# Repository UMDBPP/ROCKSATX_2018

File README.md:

# ROCKSATX_2018
BPP 2018 Rocksat - X

Payload: TERP (Tribocharging Experiment and Robotic Performance)

Contains two experiments: STAR and SCAMP

## STAR
Stratification and Tribocharging Analysis of Regolith (STAR)

## SCAMP
Space Characterization and Assessment of Manipulator Performance

# Organization
CAD/: All mechanical design files (CAD)

Payload_Integration/:  Files documenting external interfaces of TERP

SCAMP/: SCAMP-specific design files

STAR/: STAR-specific design files

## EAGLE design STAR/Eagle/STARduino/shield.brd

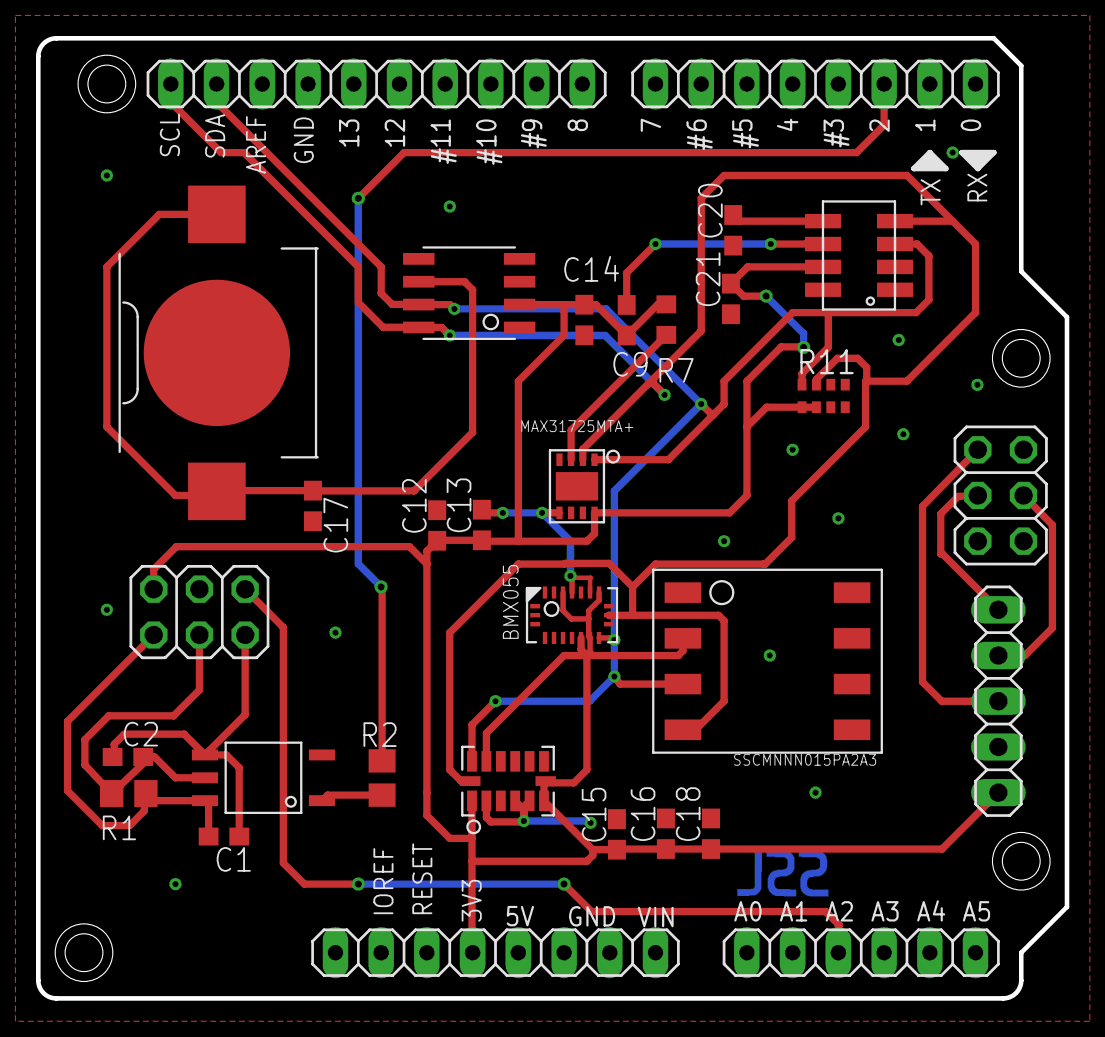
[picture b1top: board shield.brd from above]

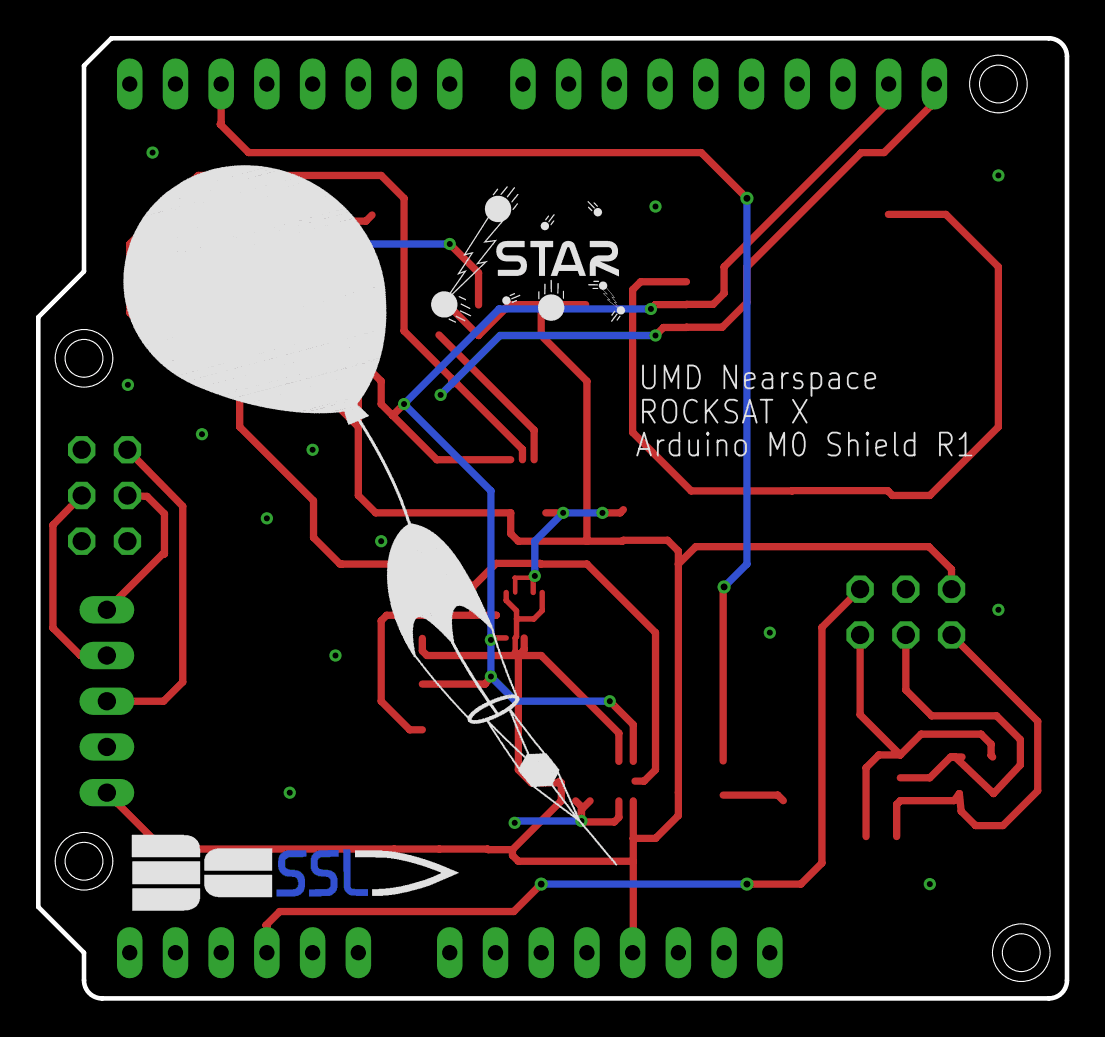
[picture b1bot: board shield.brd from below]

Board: 2 copper layers, 57.1 x 53.3 mm, 34 parts (3 on the bottom side), 16 nets.

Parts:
AD: 6x1F-H8.5; 1X06
ADXL375BCCZ: ADXL375BCCZ; LGA-14
B1: CR1025
BMX055: BMX055; LGA-20
C1, C9, C12, C13, C14, C16, C18, C20: 100nF; C0603
C2: 15pf; C0603
C15: 10uF; C0603
C17: 1nF; C0603
C21: 220nF; C0603
CC2: CC2
DS3231MZ+: DS3231MZ+; SOIC-8
IMAG2: STAR; STAR_.3IN
IOH: 10x1F-H8.5; 1X10
IOL: 8x1F-H8.5; 1X08
JP1: 1X05
JP2, JP3: 2X03
MAX31725MTA+: MAX31725MTA+; DFN-8
MOTORDRIVER: FODM8061-D; SO5
POWER: 8x1F-H8.5; 1X08
R1, R2: 442; R0805
R7: 4.7k; R0603
R11: 4.7k; 0603-ARV
U12: SSCMNNN015PA2A3; HSC-SMT-8
U$1: BALLOON
U$2: SSLORIG; SSL

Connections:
+3V3: ADXL375BCCZ.1, ADXL375BCCZ.6, ADXL375BCCZ.7, ADXL375BCCZ.12, BMX055.3, BMX055.7, BMX055.12, BMX055.13, C9.1, C12.1, C13.1, C14.1, C15.1, C16.1, C18.1, C21.2, CC2.P$7, DS3231MZ+.2, JP1.1, JP3.2, MAX31725MTA+.8, POWER.4, R7.2, R11.5, R11.6, U12.2
BIAS_REF: AD.3, JP3.6
GND: ADXL375BCCZ.2, ADXL375BCCZ.4, ADXL375BCCZ.5, B1.3, BMX055.4, BMX055.6, BMX055.17, BMX055.20, C9.2, C12.2, C13.2, C14.2, C15.2, C16.2, C17.2, C18.2, C20.1, C21.1, CC2.P$6, DS3231MZ+.5, IOH.7, JP1.2, JP2.6, JP3.4, MAX31725MTA+.4, MAX31725MTA+.5, MAX31725MTA+.6, MAX31725MTA+.7, MAX31725MTA+.9, MOTORDRIVER.P$3, POWER.6, POWER.7, U12.1
MISO: JP1.3, JP2.1
MOSI: JP1.4, JP2.4
MOTOR: IOL.3, R2.2
MOTOR_GND: C1.2, C2.2, JP3.5, MOTORDRIVER.P$4
MOTOR_SIGNAL: C2.1, JP3.3, MOTORDRIVER.P$5, R1.2
MOTOR_VCC: C1.1, JP3.1, MOTORDRIVER.P$6, R1.1
unnamed: C20.2, CC2.P$5
unnamed: MOTORDRIVER.P$1, R2.1
unnamed: MAX31725MTA+.3, R7.1
unnamed: B1.1, B1.2, C17.1, DS3231MZ+.6
SCK: JP1.5, JP2.3
SCL: ADXL375BCCZ.14, BMX055.9, CC2.P$4, DS3231MZ+.8, IOH.10, MAX31725MTA+.2, R11.3, U12.4
SDA: ADXL375BCCZ.13, BMX055.11, CC2.P$3, DS3231MZ+.7, IOH.9, MAX31725MTA+.1, R11.4, U12.3

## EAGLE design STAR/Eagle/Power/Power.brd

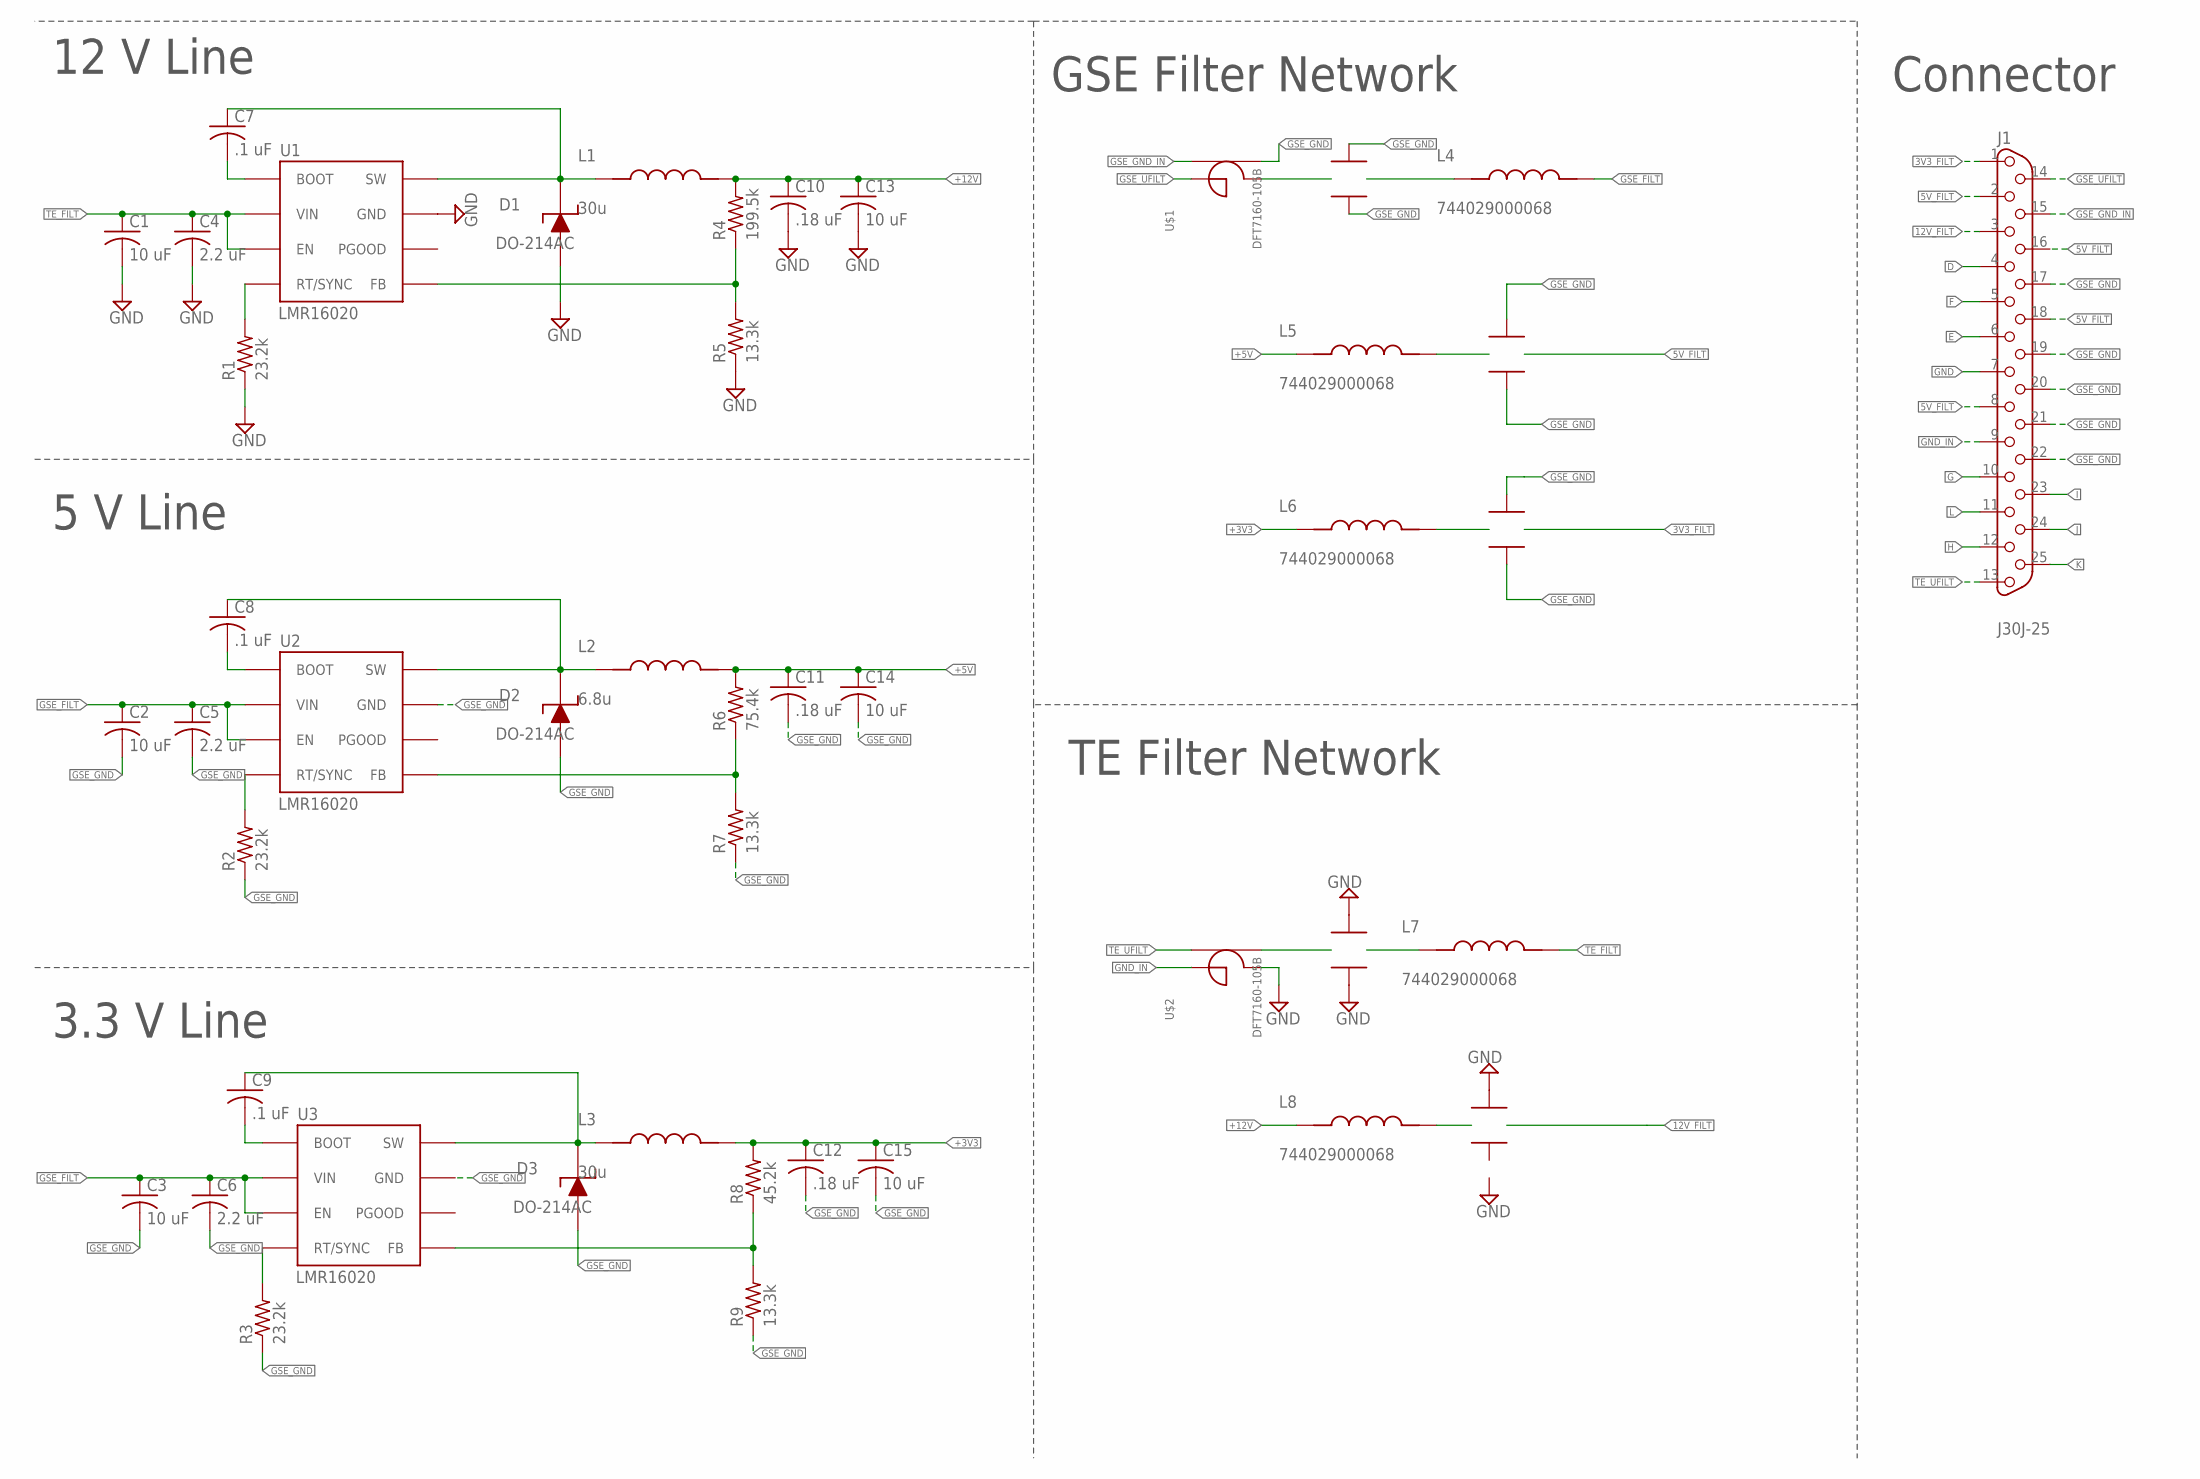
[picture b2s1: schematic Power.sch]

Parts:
C1, C2, C3: 10 uF; C1210
C4, C5, C6: 2.2 uF; C1210
C7, C8, C9: .1 uF; C0603
C10, C11, C12: .18 uF; C0603
C13, C14, C15: 10 uF; C0603
D1, D2, D3: DO-214AC
J1: J30J-25; ZKN-25
L1: 30u; 7050
L2: 6.8u; 7050
L3: 30u; 1365
L4, L5, L6, L7, L8: 744029000068; 2813
R1, R2, R3: 23.2k; R0603
R4: 199.5k; R0603
R5, R7, R9: 13.3k; R0603
R6: 75.4k; R0603
R8: 45.2k; R0603
U1, U2, U3: LMR16020; SO8
U$1, U$2: DFT7160-105B; DFT7160
U$3, U$4, U$5, U$6, U$7: 1410J0500404MXTE03; 1410

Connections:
3V3_FILT: J1.1, U$5.P$4
5V_FILT: J1.2, J1.8, J1.16, J1.18, U$4.P$4
12V_FILT: J1.3, U$7.P$4
+3V3: C12.1, C15.1, L3.P$2, L6.P$1, R8.2
+5V: C11.1, C14.1, L2.P$2, L5.P$1, R6.2
+12V: C10.1, C13.1, L1.P$2, L8.P$1, R4.2
D: J1.4
E: J1.6
F: J1.5
G: J1.10
GND: C1.2, C4.2, C10.2, C13.2, D1.P$1, J1.7, R1.1, R5.1, U1.P$7 (GND), U1.PAD (GND), U$2.P$4, U$6.P$2, U$6.P$3, U$7.P$3
GND_IN: J1.9, U$2.P$1
GSE_FILT: C2.1, C3.1, C5.1, C6.1, L4.P$2, U2.P$2 (VIN), U2.P$3 (EN), U3.P$2 (VIN), U3.P$3 (EN)
GSE_GND: C2.2, C3.2, C5.2, C6.2, C11.2, C12.2, C14.2, C15.2, D2.P$1, D3.P$1, J1.17, J1.19, J1.20, J1.21, J1.22, R2.1, R3.1, R7.1, R9.1, U2.P$7 (GND), U2.PAD (GND), U3.P$7 (GND), U3.PAD (GND), U$1.P$3, U$3.P$2, U$3.P$3, U$4.P$2, U$4.P$3, U$5.P$2, U$5.P$3
GSE_GND_IN: J1.15, U$1.P$2
GSE_UFILT: J1.14, U$1.P$1
H: J1.12
I: J1.23
J: J1.24
K: J1.25
L: J1.11
unnamed: R3.2, U3.P$4 (RT/SYNC)
unnamed: C9.1, D3.P$2, L3.P$1, U3.P$8 (SW)
unnamed: R2.2, U2.P$4 (RT/SYNC)
unnamed: C8.2, U2.P$1 (BOOT)
unnamed: C8.1, D2.P$2, L2.P$1, U2.P$8 (SW)
unnamed: C9.2, U3.P$1 (BOOT)
unnamed: R1.2, U1.P$4 (RT/SYNC)
unnamed: R8.1, R9.2, U3.P$5 (FB)
unnamed: R6.1, R7.2, U2.P$5 (FB)
unnamed: C7.2, U1.P$1 (BOOT)
unnamed: C7.1, D1.P$2, L1.P$1, U1.P$8 (SW)
unnamed: R4.1, R5.2, U1.P$5 (FB)
unnamed: U$1.P$4, U$3.P$4
unnamed: U$2.P$3, U$6.P$5
unnamed: L4.P$1, U$3.P$5
unnamed: L5.P$2, U$4.P$5
unnamed: L6.P$2, U$5.P$5
unnamed: L7.P$1, U$6.P$4
unnamed: L8.P$2, U$7.P$5
TE_FILT: C1.1, C4.1, L7.P$2, U1.P$2 (VIN), U1.P$3 (EN)
TE_UFILT: J1.13, U$2.P$2

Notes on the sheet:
12 V Line
5 V Line
3.3 V Line
GSE Filter Network
TE Filter Network
Connector

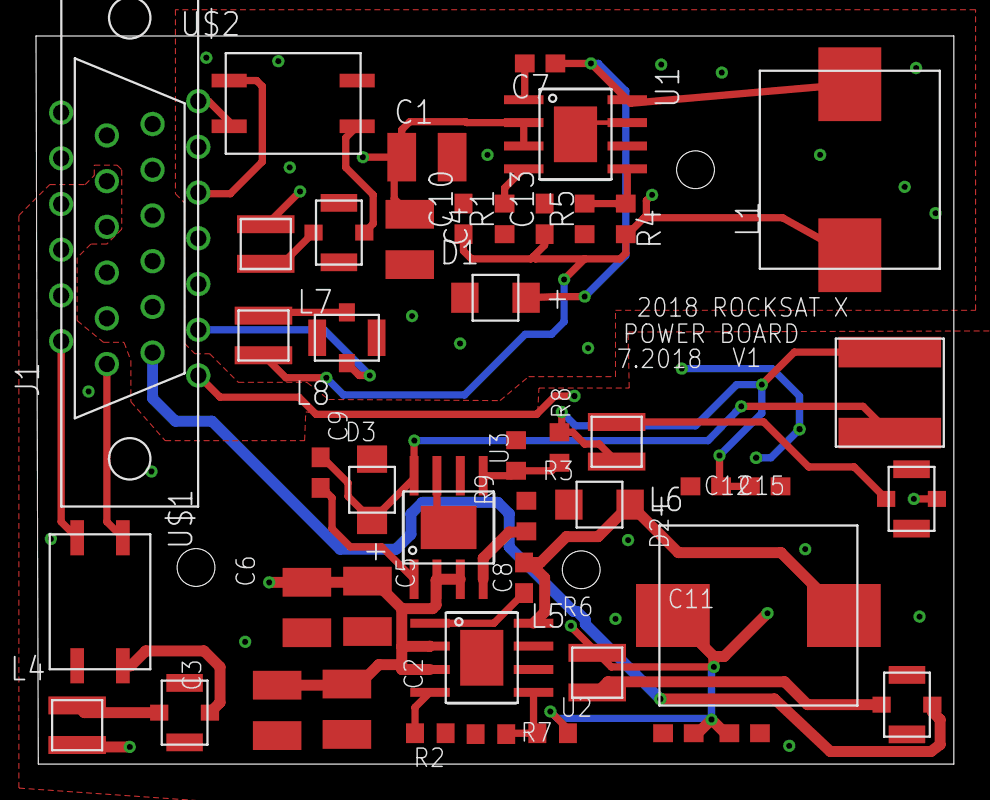
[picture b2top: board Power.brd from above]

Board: 2 copper layers, 51.0 x 40.4 mm, 46 parts (0 on the bottom side), 33 nets.

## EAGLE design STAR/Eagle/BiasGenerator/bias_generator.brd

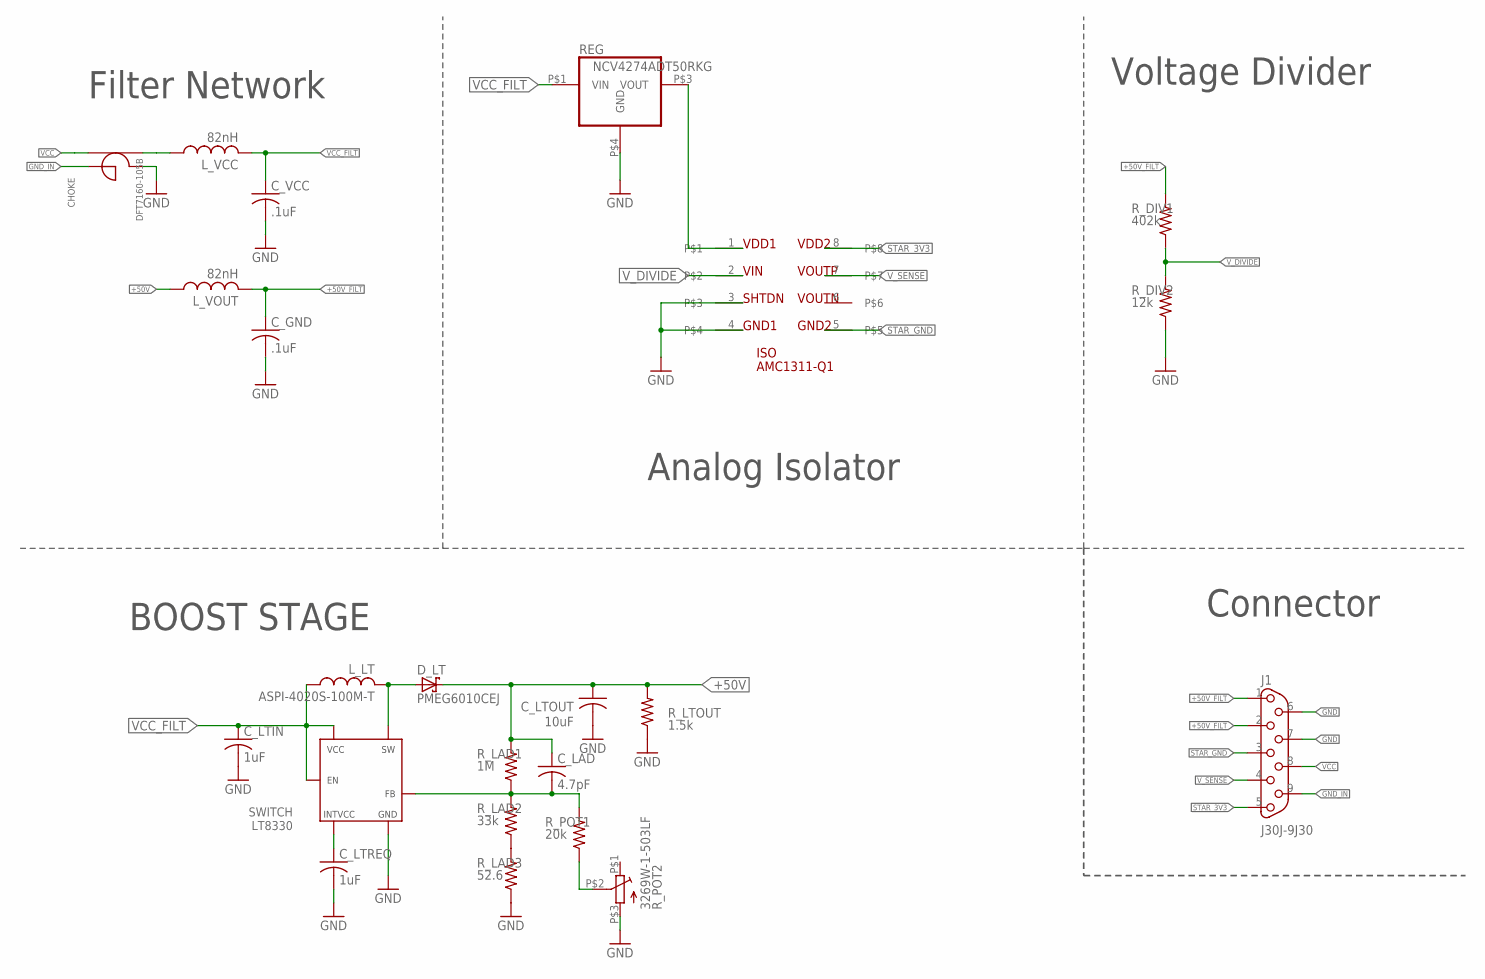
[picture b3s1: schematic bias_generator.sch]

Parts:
CHOKE: DFT7160-105B; DFT7160
C_GND: .1uF; C0603
C_LAD: 4.7pF; 0603
C_LTIN: 1uF; 0603
C_LTOUT: 10uF; 2J-LEAD
C_LTREQ: 1uF; 0603
C_VCC: .1uF; C0603
D_LT: PMEG6010CEJ; SOD323
ISO: AMC1311-Q1; SOIC8
J1: J30J-9J30; ZKN-9-J30
L_LT: ASPI-4020S-100M-T; 4MM
L_VCC: 82nH; C0603
L_VOUT: 82nH; C0603
REG: NCV4274ADT50RKG; DPAK
R_DIV1: 402k; R0603
R_DIV2: 12k; R0603
R_LAD1: 1M; R0603
R_LAD2: 33k; R0603
R_LAD3: 52.6; R0603
R_LTOUT: 1.5k; R2512
R_POT1: 20k; R0603
R_POT2: 3269W-1-503LF; POTENTIOMETER
SWITCH: LT8330; 8-DFN

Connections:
5V_REG: ISO.1, REG.P$3 (VOUT)
+50V: C_LAD.1, C_LTOUT.P$1 (1), D_LT.P$2 (C), L_VOUT.1, R_LAD1.2, R_LTOUT.2
+50V_FILT: C_GND.1, J1.1, J1.2, L_VOUT.2, R_DIV1.2
FBX: C_LAD.2, R_LAD1.1, R_LAD2.2, R_POT1.2, SWITCH.P$1 (FB)
GND: CHOKE.P$4 (L1OUT), C_GND.2, C_LTIN.2, C_LTOUT.P$2 (2), C_LTREQ.2, C_VCC.2, ISO.3, ISO.4, J1.6, J1.7, REG.P$4 (GND), R_DIV2.1, R_LAD3.1, R_LTOUT.1, R_POT2.P$3, SWITCH.P$5 (GND), SWITCH.P$9 (GND)
GND_IN: CHOKE.P$1 (L1IN), J1.9
INTVCC: C_LTREQ.1, SWITCH.P$7 (INTVCC)
unnamed: CHOKE.P$3 (L2OUT), L_VCC.1
unnamed: R_POT1.1, R_POT2.P$2
unnamed: R_LAD2.1, R_LAD3.2
STAR_3V3: ISO.8, J1.5
STAR_GND: ISO.5, J1.3
SW: D_LT.P$1 (A), L_LT.P$2 (2), SWITCH.P$3 (SW), SWITCH.P$4 (SW)
VCC: CHOKE.P$2 (L2IN), J1.8
VCC_FILT: C_LTIN.1, C_VCC.1, L_LT.P$1 (1), L_VCC.2, REG.P$1 (VIN), SWITCH.P$6 (VCC), SWITCH.P$8 (EN)
V_DIVIDE: ISO.2, R_DIV1.1, R_DIV2.2
V_SENSE: ISO.7, J1.4

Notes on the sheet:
BOOST STAGE
Voltage Divider
Connector
Filter Network
Analog Isolator

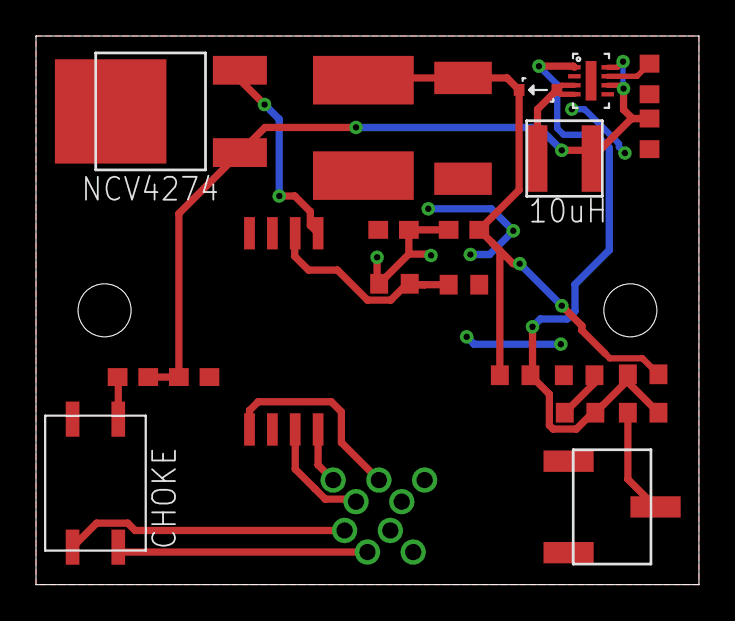
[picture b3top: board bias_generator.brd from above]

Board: 2 copper layers, 36.8 x 30.5 mm, 23 parts (0 on the bottom side), 17 nets.

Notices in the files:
parts and their libraries:
SparkFun-Passives: Licensing: CC v3.0 Share-Alike You are welcome to use this library for commercial purposes.
